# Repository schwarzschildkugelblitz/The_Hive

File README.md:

# The Hive 
The Following is Team Placeholders Solution to Flipkart's Grid 3.0

## About Grid 3.0

GRiD is Flipkart’s Flagship Engineering Campus Challenge which provides you the opportunity to apply your technical knowledge and skills, to compete and complete key challenges.

In its third edition, Flipkart GRiD becomes bigger & better, bringing Live Problem Statements from the world of E-Commerce to the brightest minds of India and lets you put your capabilities to the ultimate test.
## Problem  Statement

### Relay race - 4 Robots

1. Each robot has a package on top
2. Start positions are S1, S2, S3 & S4
3. Bot from S1 is expected to go to D1, Bot from S2 is expected to go to D2 and so on...
4. On start - Bot in the S1 location is expected to go to D1
5. On reaching D1 it should drop the item beyond the wall
6. Once the bot comes back to S1 (Completely inside S1 square), only then Bot from S2 can start
7. Race is over when S4 robot comes back to its square after dropping the parcel
No touching of the robots hardware/software is allowed once the race starts - Completely autonomous robots
Overall Arena size is 5 x 10ft

● Each block is 6x6in

● The grid is 1 cm tape / marking

● The brown line next to D1, D2, D3 & D4 is a 1-inch height wall

### Judging Criteria for Round I

Top 100 teams to finish the relay race (shortest time) - make it to Round II

### Deliverables for Round I
1. Pictures of Robots
2. Time taken to complete the relay race
3. Uninterrupted Video of the Relay Race - with Timer overlayed to indicate start and end of race - This
can be shot with a handheld or phone camera
4. Uninterrupted Video of Live Image Processing - with Timer overlayed to show how robots are being
tracked in real-time

## About The Team 

The Team consisted of the following members 
1. Harshit Batra 
2. Tanmay Vadhera
3. Mudit Aggarwal
4. Rohan Deswal
5. Drishti Adlakha 
6. Arjun Narula 
7. Harshit Kapoor
8. Mukul Gupta 
9. Vikas Poddar 
10. Soham

## Achitectrue

### Queen Tracking System 
### Transmission System
### Worker bee 

## Mechanical

## Electronics 
### Power system 
the worker bee is power by powerfull 7.2 V 2500 mah li-ion Battery

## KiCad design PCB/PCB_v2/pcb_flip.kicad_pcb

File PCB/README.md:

# PCB for Bot 

## Iteration 1 

Designed By Team Placeholders and Manufactured By PCB Powers 

### Dimensions

### Parts 

1. Arduino nano 
2. L293D
3. Power circuit 
4. NRF24 

### Funionality 

1. Driving bot's N20 Motor 
2. Driving bot's Servo Motor  
3. Receiving Data from Central Tracking system 

### Schmatic Diagram 

### 3D view 

## Iteration 2

Designed By Team Placeholders and Manufactured at CEDT lab,NSUT

### What's new 

1. Added boost cicuit 
2. Changed dimensions 

### Parts 

1. Arduino nano 
2. L293D
3. Power circuit 
4. NRF24 

### Funionality 
1. Driving bot's N20 Motor 
2. Driving bot's Servo Motor  
3. Receiving Data from Central Tracking system 

### Schmatic Diagram 

### 3D view

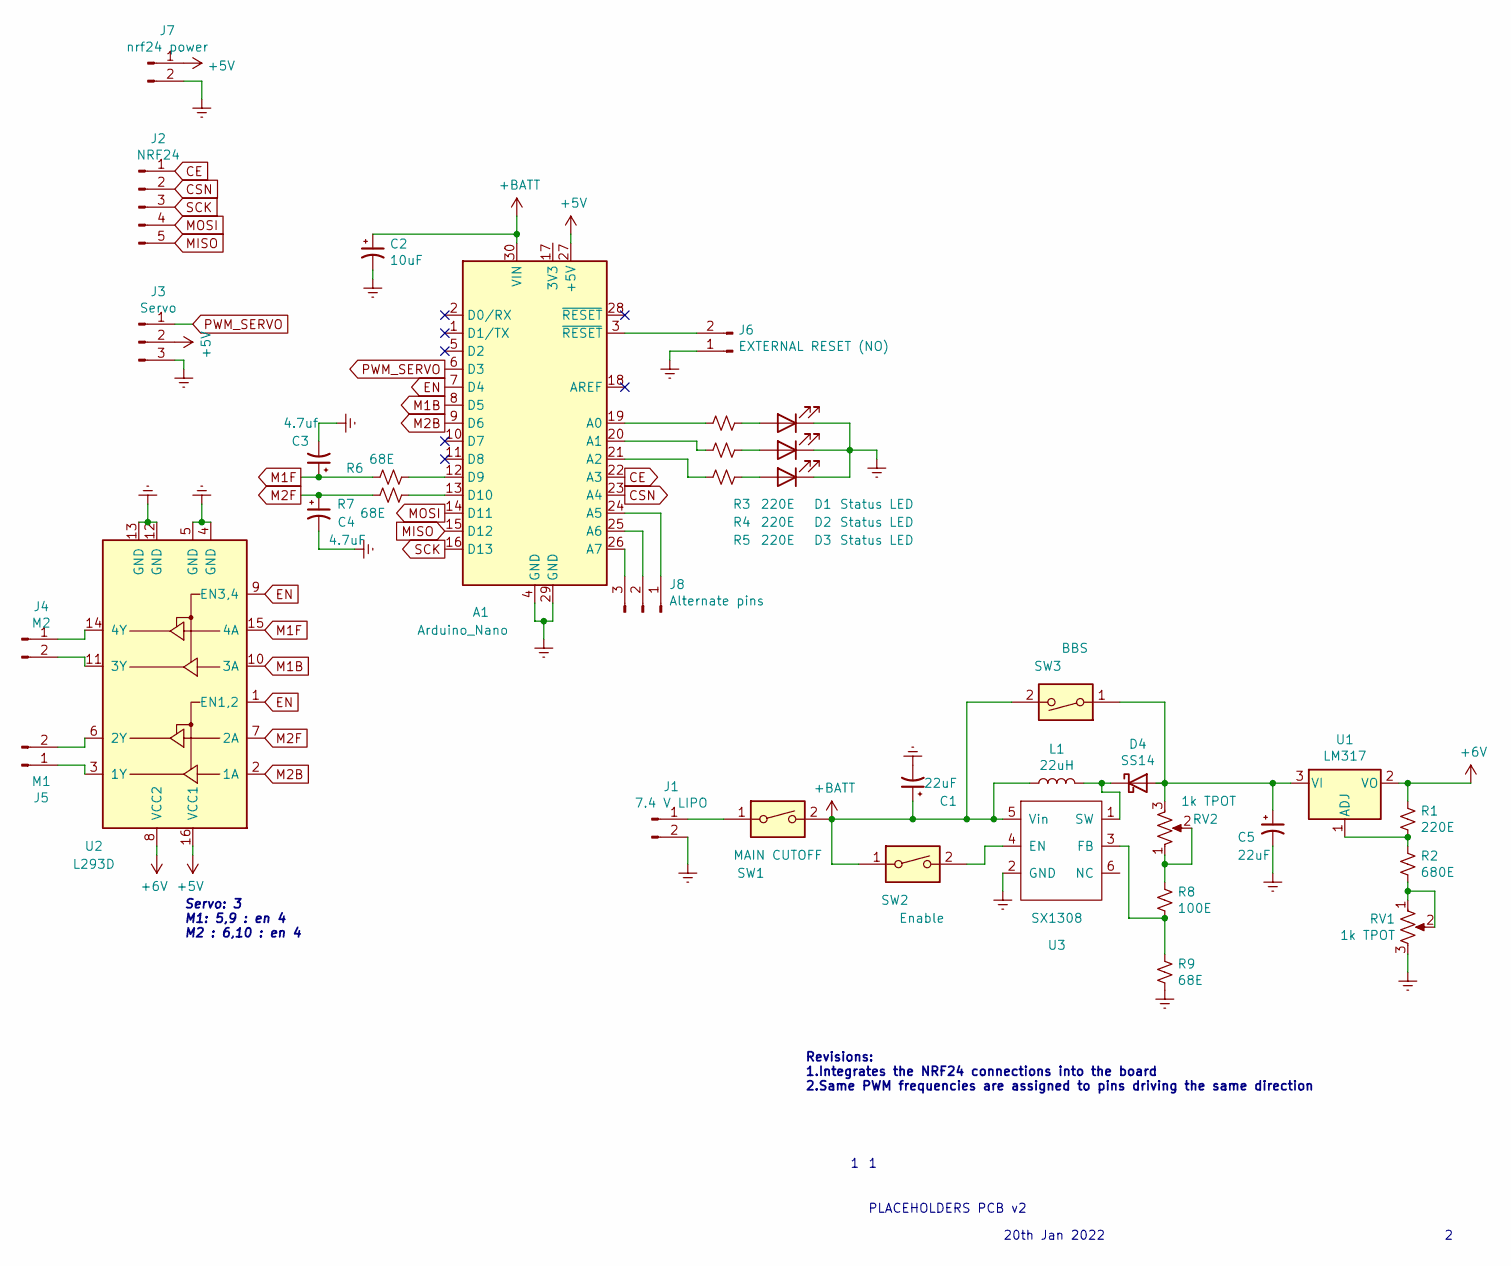
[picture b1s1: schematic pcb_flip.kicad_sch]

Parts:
A1: Arduino_Nano
C1, C5: 22uF; C_1206_3216Metric_Pad1.33x1.80mm_HandSolder
C2: 10uF; CP_EIA-3528-12_Kemet-T_Pad1.50x2.35mm_HandSolder
C3: 4.7uf; CP_EIA-3528-12_Kemet-T_Pad1.50x2.35mm_HandSolder
C4: 4.7uF; CP_EIA-3528-12_Kemet-T_Pad1.50x2.35mm_HandSolder
D1, D2, D3: Status LED; LED_D5.0mm_IRGrey
D4: SS14; D_1210_3225Metric_Pad1.42x2.65mm_HandSolder
J1: 7.4 V LIPO; JST_XH_B2B-XH-A_1x02_P2.50mm_Vertical
J2: NRF24; PinHeader_1x05_P2.54mm_Vertical
J3: Servo; PinHeader_1x03_P2.54mm_Vertical
J4: M2; TerminalBlock_Phoenix_MKDS-1,5-2_1x02_P5.00mm_Horizontal
J5: M1; TerminalBlock_Phoenix_MKDS-1,5-2_1x02_P5.00mm_Horizontal
J6: EXTERNAL RESET (NO); PinHeader_1x02_P2.54mm_Vertical
J7: nrf24 power; PinHeader_1x02_P2.54mm_Vertical
J8: Alternate pins; PinHeader_1x03_P2.54mm_Vertical
L1: 22uH; L_Radial_D6.0mm_P4.00mm
R1, R3, R4, R5: 220E; R_0805_2012Metric_Pad1.20x1.40mm_HandSolder
R2: 680E; R_0805_2012Metric_Pad1.20x1.40mm_HandSolder
R6, R7: 68E; R_0805_2012Metric_Pad1.20x1.40mm_HandSolder
R8: 100E; R_0805_2012Metric_Pad1.20x1.40mm_HandSolder
R9: 68E; C_0805_2012Metric_Pad1.18x1.45mm_HandSolder
RV1, RV2: 1k TPOT; Potentiometer_Bourns_3296W_Vertical
SW1: MAIN CUTOFF; JST_XH_B2B-XH-A_1x02_P2.50mm_Vertical
SW2: Enable; SolderJumper-2_P1.3mm_Open_TrianglePad1.0x1.5mm
SW3: BBS; SolderJumper-2_P1.3mm_Open_TrianglePad1.0x1.5mm
U1: LM317; TO-220-3_Vertical
U2: L293D; DIP-16_W7.62mm_Socket
U3: SX1308; SOT-23-6_Handsoldering

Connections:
+5V: A1.27 (+5V), J3.2, J7.1, U2.16 (VCC1); also elsewhere on the board
+6V: R1.1, U1.2 (VO), U2.8 (VCC2)
+BATT: A1.30 (VIN), C1.1, C2.1, L1.1, SW1.2, SW2.1, SW3.2, U3.5 (Vin)
CE: A1.22 (A3), J2.1; also elsewhere on the board
CSN: A1.23 (A4), J2.2; also elsewhere on the board
EN: A1.7 (D4), U2.1 (EN1,2), U2.9 (EN3,4)
Earth: A1.4 (GND), A1.29 (GND), C1.2, C2.2, C3.2, C4.2, C5.2, D1.1 (K), D2.1 (K), D3.1 (K), J1.2, J3.3, J6.1, J7.2, R9.2, RV1.3, U2.4 (GND), U2.5 (GND), U2.12 (GND), U2.13 (GND), U3.2 (GND); also elsewhere on the board
M1B: A1.8 (D5), U2.10 (3A)
M1F: C3.1, R6.2, U2.15 (4A)
M2B: A1.9 (D6), U2.2 (1A)
M2F: C4.1, R7.2, U2.7 (2A)
MISO: A1.15 (D12), J2.5; also elsewhere on the board
MOSI: A1.14 (D11), J2.4; also elsewhere on the board
unnamed: A1.3 (~RESET), J6.2
unnamed: A1.12 (D9), R6.1
unnamed: A1.13 (D10), R7.1
unnamed: A1.19 (A0), R3.2
unnamed: A1.20 (A1), R4.2
unnamed: A1.21 (A2), R5.2
unnamed: A1.24 (A5), J8.1
unnamed: A1.25 (A6), J8.2
unnamed: A1.26 (A7), J8.3
unnamed 22: C5.1, D4.2 (A), RV2.3, SW3.1, U1.3 (VI); also elsewhere on the board
unnamed: D1.2 (A), R3.1
unnamed: D2.2 (A), R4.1
unnamed: D3.2 (A), R5.1
unnamed 26: D4.1 (K), L1.2, U3.1 (SW); also elsewhere on the board
unnamed: J1.1, SW1.1
unnamed: J4.1, U2.14 (4Y)
unnamed: J4.2, U2.11 (3Y)
unnamed: J5.1, U2.3 (1Y)
unnamed: J5.2, U2.6 (2Y)
unnamed: R1.2, R2.1, U1.1 (ADJ)
unnamed: R2.2, RV1.1, RV1.2
unnamed: R8.1, RV2.1, RV2.2
unnamed: R8.2, R9.1, U3.3 (FB)
unnamed: SW2.2, U3.4 (EN)
PWM_SERVO: A1.6 (D3), J3.1
SCK: A1.16 (D13), J2.3; also elsewhere on the board

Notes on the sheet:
20th Jan 2022
PLACEHOLDERS PCB v2
Servo: 3 M1: 5,9 : en 4 M2 : 6,10 : en 4
Revisions: 1.Integrates the NRF24 connections into the board 2.Same PWM frequencies are assigned to pins driving the same direction

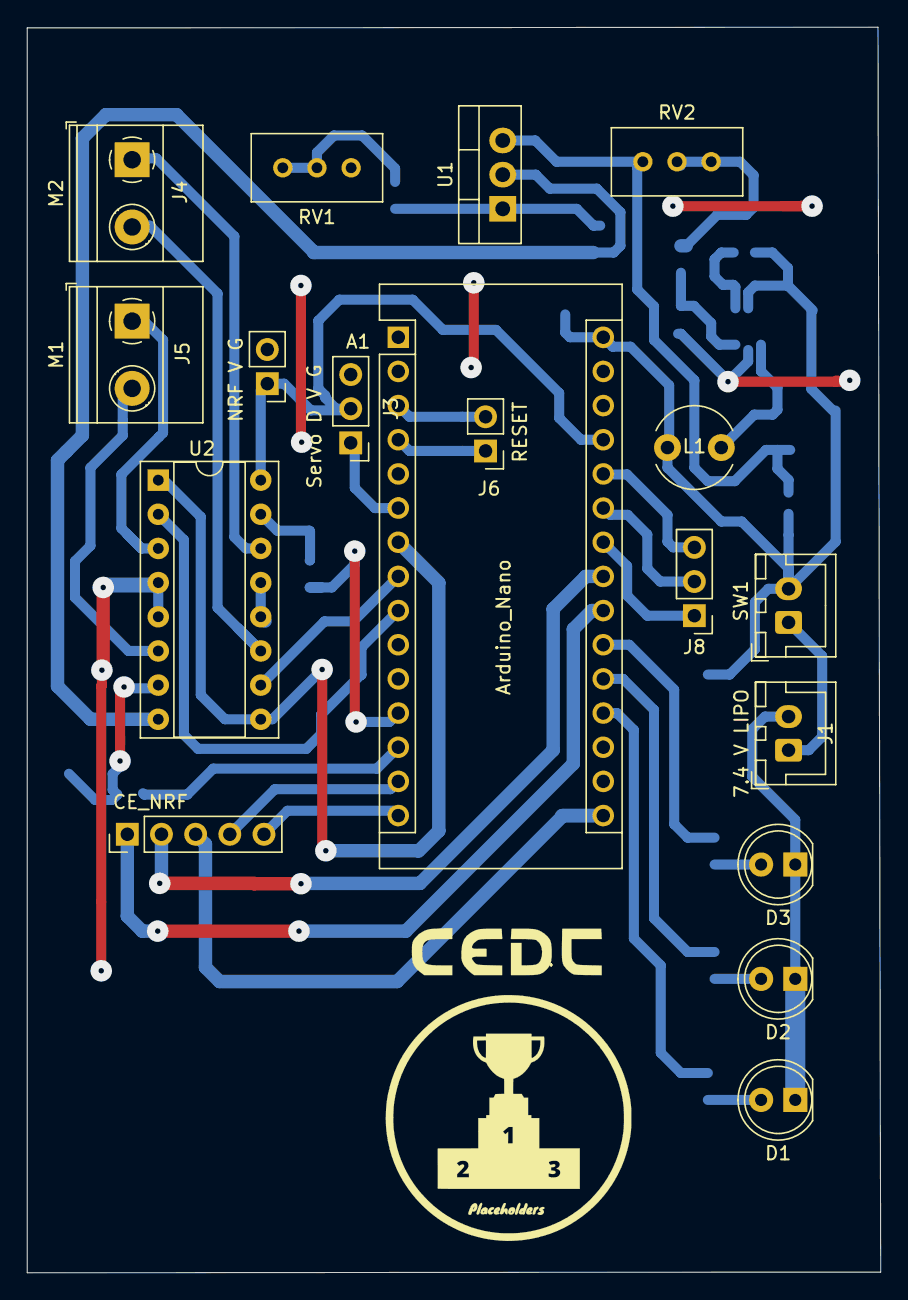
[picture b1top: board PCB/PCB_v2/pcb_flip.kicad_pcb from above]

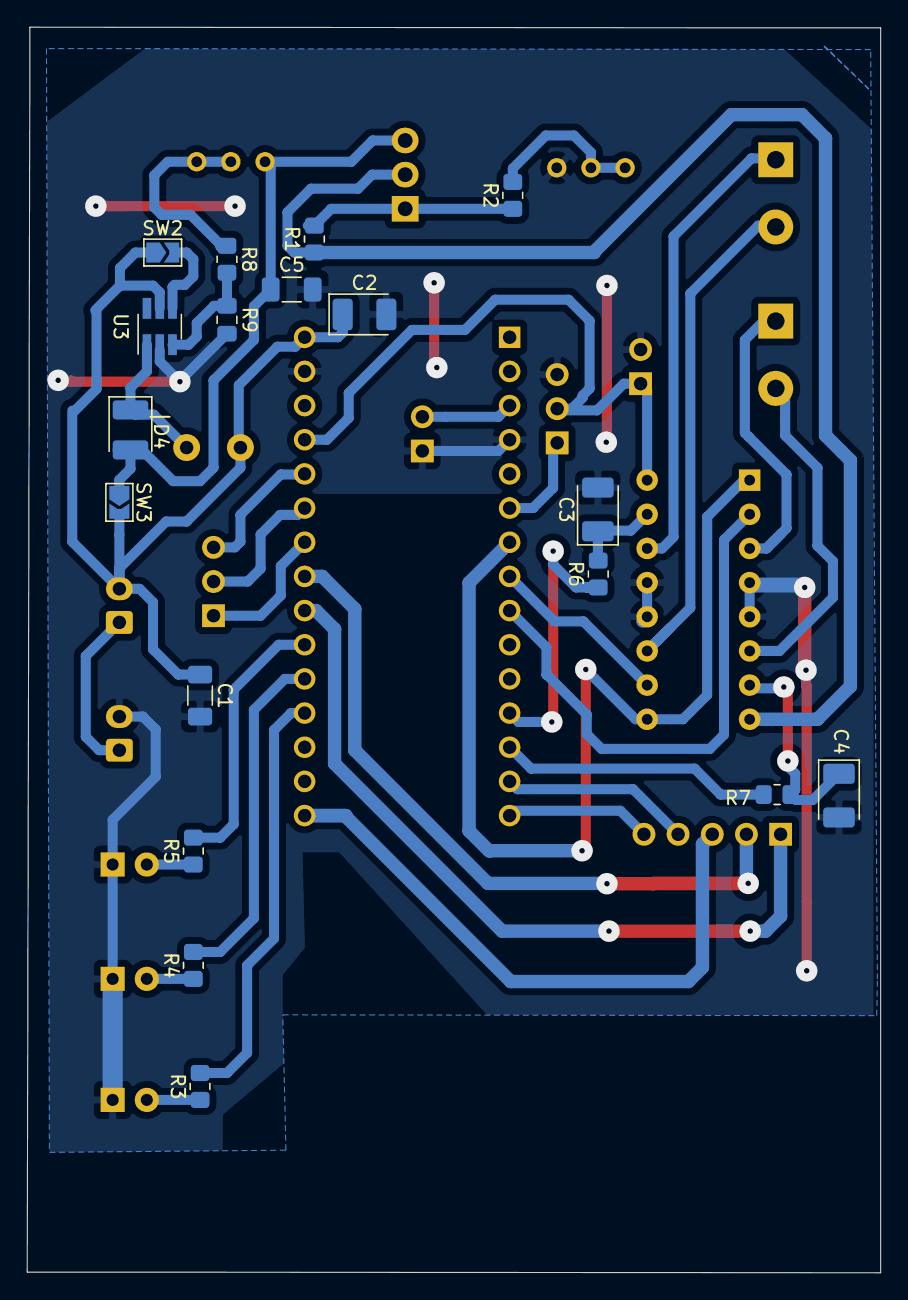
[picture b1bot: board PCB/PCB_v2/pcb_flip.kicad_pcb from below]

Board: 2 copper layers, 63.4 x 92.6 mm, 38 parts (18 on the bottom side), 39 nets.

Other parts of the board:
CE_NRF: NRF24; PinHeader_1x05_P2.54mm_Vertical
NRF V G: nrf24 power; PinHeader_1x02_P2.54mm_Vertical
RV2-24/01/2022: LOGO; placeholders
T V: LOGO; epp
|D4: SS14; D_1210_3225Metric_Pad1.42x2.65mm_HandSolder

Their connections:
+5V: NRF V G.1; also elsewhere on the board
CE: CE_NRF.1; also elsewhere on the board
CSN: CE_NRF.2; also elsewhere on the board
Earth: NRF V G.2; also elsewhere on the board
MISO: CE_NRF.5; also elsewhere on the board
MOSI: CE_NRF.4; also elsewhere on the board
unnamed 22: |D4.2; also elsewhere on the board
unnamed 26: |D4.1; also elsewhere on the board
SCK: CE_NRF.3; also elsewhere on the board

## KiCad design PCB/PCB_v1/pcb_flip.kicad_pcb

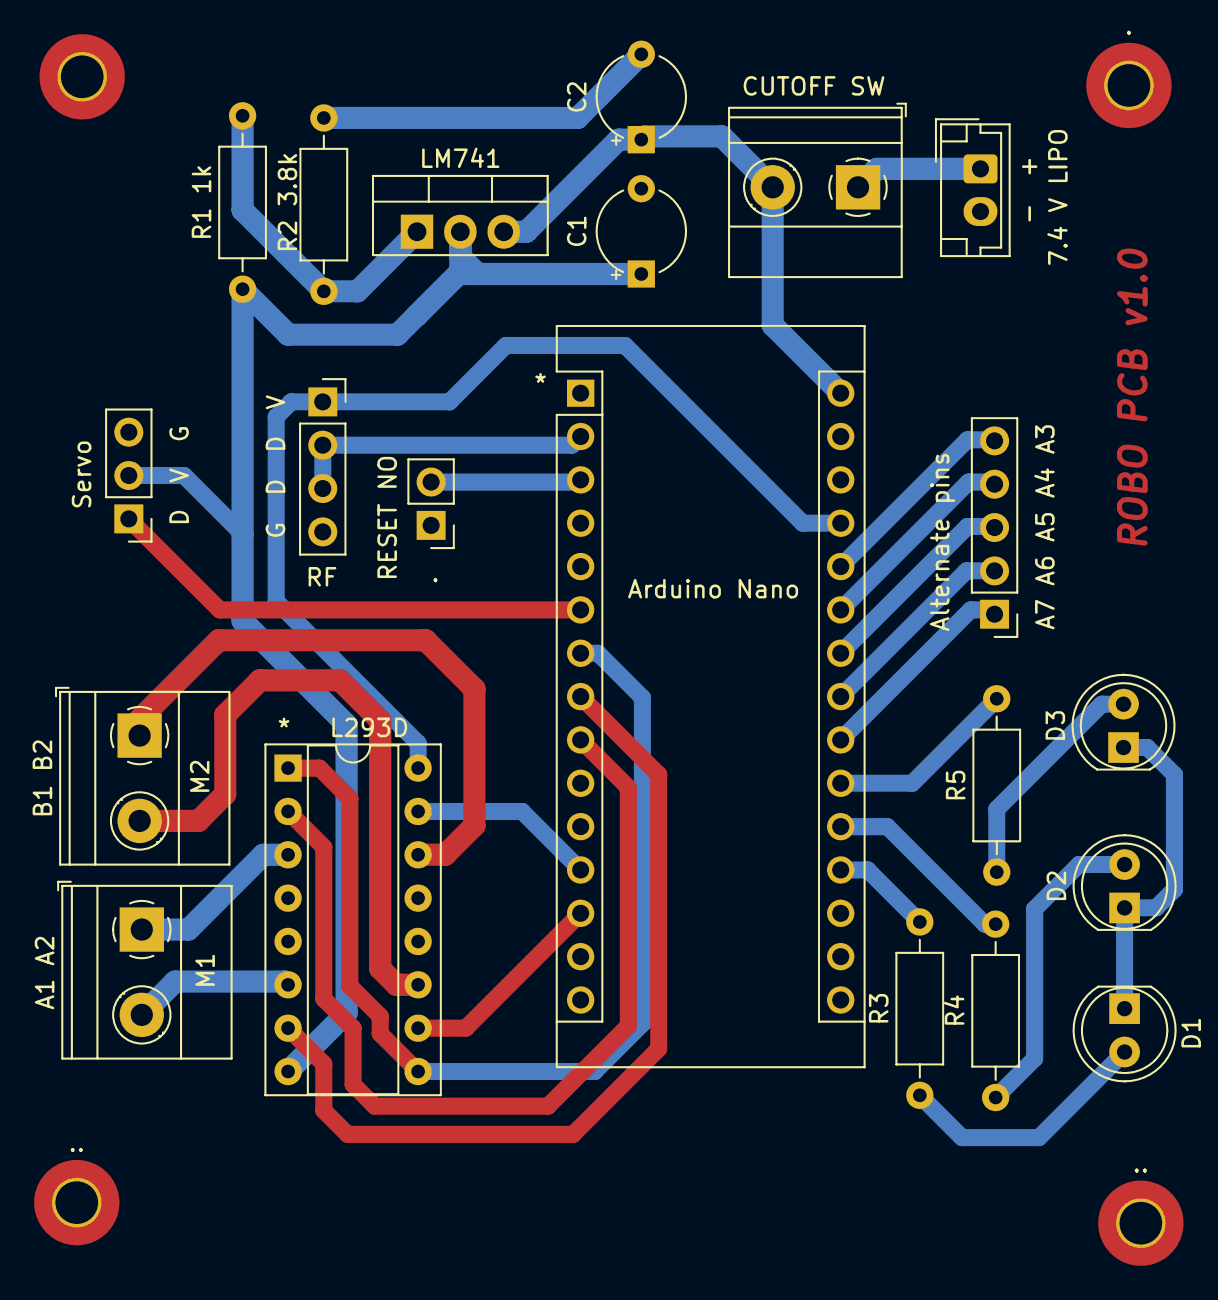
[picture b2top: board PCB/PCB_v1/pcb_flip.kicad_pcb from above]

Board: 2 copper layers, 25 parts (0 on the bottom side), 29 nets.

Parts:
 : .; MountingHole_2.5mm_Pad_TopBottom
*   L293D: L293D; DIP-16_W7.62mm_Socket
-  +: 7.4 V LIPO; JST_EH_B2B-EH-A_1x02_P2.50mm_Vertical
., .., ..#2: .; MountingHole_2.5mm_Pad_TopBottom
.#2: RESET NO; PinHeader_1x02_P2.54mm_Vertical
A7 A6 A5 A4 A3: Alternate pins; PinHeader_1x05_P2.54mm_Vertical
Arduino Nano: *; Arduino_Nano
C1, C2: 1uf; CP_Radial_Tantal_D5.0mm_P5.00mm
CUTOFF SW: MAIN CUTOFF; TerminalBlock_Phoenix_MKDS-1,5-2_1x02_P5.00mm_Horizontal
D1, D2, D3: Status LED; LED_D5.0mm
D  V  G: Servo; PinHeader_1x03_P2.54mm_Vertical
LM741: LM317; TO-220-3_Vertical
M1: A1 A2; TerminalBlock_Phoenix_MKDS-1,5-2_1x02_P5.00mm_Horizontal
M2: B1 B2; TerminalBlock_Phoenix_MKDS-1,5-2_1x02_P5.00mm_Horizontal
R1 1k: 1k; R_Axial_DIN0207_L6.3mm_D2.5mm_P10.16mm_Horizontal
R2 3.8k: 3.8k; R_Axial_DIN0207_L6.3mm_D2.5mm_P10.16mm_Horizontal
R3, R4, R5: 220E; R_Axial_DIN0207_L6.3mm_D2.5mm_P10.16mm_Horizontal
RF: G D D V; PinSocket_1x04_P2.54mm_Vertical

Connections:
+5V: * L293D.16, Arduino Nano.27, RF.1
+6V: * L293D.8, C1.1, D V G.2, LM741.2, R1 1k.1
+BATT: Arduino Nano.30, C2.1, CUTOFF SW.2, LM741.3
Earth: * L293D.4, * L293D.5, * L293D.12, * L293D.13, - +.2, .#2.1, Arduino Nano.4, Arduino Nano.29, C1.2, C2.2, D1.1, D2.1, D3.1, D V G.3, R2 3.8k.2, RF.4
unnamed: Arduino Nano.2, RF.2, RF.3
unnamed: .#2.2, Arduino Nano.3
unnamed: Arduino Nano.6, D V G.1
unnamed: * L293D.1, * L293D.9, Arduino Nano.7
unnamed: * L293D.7, Arduino Nano.8
unnamed: * L293D.2, Arduino Nano.9
unnamed: * L293D.15, Arduino Nano.12
unnamed: * L293D.10, Arduino Nano.13
unnamed: Arduino Nano.19, R3.2
unnamed: Arduino Nano.20, R4.2
unnamed: Arduino Nano.21, R5.2
unnamed: A7 A6 A5 A4 A3.1, Arduino Nano.22
unnamed: A7 A6 A5 A4 A3.2, Arduino Nano.23
unnamed: A7 A6 A5 A4 A3.3, Arduino Nano.24
unnamed: A7 A6 A5 A4 A3.4, Arduino Nano.25
unnamed: A7 A6 A5 A4 A3.5, Arduino Nano.26
unnamed: D1.2, R3.1
unnamed: D2.2, R4.1
unnamed: D3.2, R5.1
unnamed: - +.1, CUTOFF SW.1
unnamed: * L293D.14, M2.1
unnamed: * L293D.11, M2.2
unnamed: * L293D.3, M1.1
unnamed: * L293D.6, M1.2
unnamed: LM741.1, R1 1k.2, R2 3.8k.1

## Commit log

2021-06-25 created folder for machine learning model
2021-06-26 Create pcb_design
2021-06-26 Add files via upload
    Main circuit board for the robot.
2021-06-28 Implemented tracking markers and added perspective correction
2021-06-29 fixed some array parsing errors
2021-07-28 Updated problem statement and other pdfs
2021-08-31 Increased number of markers
2021-09-04 added text to video
2021-09-04 Rename main_body/ROBOT_W_changes v3.step to mechanical/ ROBOT_W_changes v3.step
2021-09-04 Create h
2021-09-04 added official information Given by the Organizer
2021-09-04 added readme
2021-09-04 Rename mechanical/ROBOT_W_changes v3.step to CAD_Model/ROBOT_W_changes v3.step
2021-09-05 Serial and Control classes added, code made more generalized
2021-09-05 Doc strings added
2021-09-07 added communication detalis
    0-3 bits address
    case 1 - angle(in degrees) 2 decimal precision
    - distance (in cm ) 2 decimal places
    case 2 - 0 stop 1 right 2 left 3 drop 4 slow drive
2021-09-10 Rename servo_calibration.ino to worker_bee/servo_calibration.ino
2021-09-19 PID system added, initial system altered, code is undocumented
2021-09-20 Rename serial_comm/serial_comm/reception/reception.ino to worker_bee/reception/reception.ino
2021-09-20 Rename serial_comm/serial_comm/transmission/transmission.ino to workerbee/transmission/transmission.ino
2021-09-20 Rename workerbee/transmission/transmission.ino to worker_beetransmissiontransmission.ino
2021-09-20 Rename worker_beetransmissiontransmission.ino to worker_bee/transmission/transmission.ino
2021-09-20 Create miscellaneous
2021-09-20 Rename miscellaneous to Miscellaneous/hhh
2021-09-28 Using only single camera, PID system updated, code refactored
2021-09-29 Final working code for round 1 tuned PID, changes in path calculation
2021-09-29 changed special commands
2021-10-01 minor changes made code better
2021-10-01 fixed minor bug
2021-10-03 Some changes to docstrings and refactoring
2021-11-09 Testing Edit
2021-12-01 frontend layout updated
2021-12-24 1st Round final working code
2021-12-24 changed design of dashboard
    changes made in frontend
2021-12-25 all files added
2021-12-25 Frontend updated
    front end layout changed and improved
2021-12-25 Frontend updated
    frontend layout changed and improved
2021-12-26 added live video
2021-12-29 changes in backend
2021-12-29 minor changes
2021-12-29 Round 2 1st attempt code
2022-01-01 Add files via upload
    stop button integration
2022-01-02 round 2 code,m PID adjusted
2022-01-04 Added Astar Visualisation Tool
2022-01-04 Adjusted PID Values with True Divide Error Fix
2022-01-04 Updated Value Adjustments for difference in motor speeds
2022-01-04 Added Code for KIll Switch
2022-01-04 PEP8 Compliance Check
2022-01-04 Revert "Add files via upload"
2022-01-04 Stop Button Integration in round_2 branch
2022-01-05 round 2 collision detection and multiprocessing
2022-01-06 without pathfinding implemented
2022-01-06 without pathfinding implemented and few runs tested
2022-01-07 Path Finding Completed
2022-01-07 pathfinding ind-1 completed and ind-2 to be checked 😊
2022-01-07 minor changes in frontend fixed minor bugs
2022-01-08 Updated astar.py added check to minimize turning by changing heuritic measurement
    minimized turns in path finding
2022-01-08 updated astar.py
2022-01-08 Path Finding And Drop Alignment
2022-01-08 Reverted Back to Pre Drop AligningRevert "updated astar.py"
    This reverts commit cbd10ec3fde4a2e8de5573e28950942e1b3babec.
2022-01-08 serial pipe implemented
2022-01-08 PathFinder Drop Alignment Implemented
2022-01-10 Refactored Path Finder and Astar and seperated into two files
2022-01-10 Path Finder and Astar Refactored
2022-01-10 Initial Path Alignment Update
2022-01-10 priority target hit check implemented
2022-01-10 turning to be tuned
2022-01-12 round 2 working for 1 bot
2022-01-12 Space Offset Updated
2022-01-13 Additional Drop Chute Offset Added
2022-01-14 hot milfs in my area
2022-01-17 added error in astar
2022-01-17 testing improved astar
2022-01-18 1 bot properly working
2022-01-18 Alternate Path Gen Implemented
2022-01-18 Alternate Path Gen Bug Fixxes
2022-01-18 almost ready for testing round 2 multiple
2022-01-18 almost ready for testing round 2 multiple (fixed)
2022-01-18 A* Nuked
2022-01-19 control system minor changes
2022-01-19 Round 2 smart threshold to be implemented
2022-01-19 1 test done
2022-01-20 command delay properly added
2022-01-25 Post Round 2 Submission
2022-01-27 PEP8 Compliance Update
2022-01-27 added readme for PCB
2022-01-27 Added boost circuitry and optimized pin mappings
2022-01-27 grid added to frontend
2022-01-28 documentation added
2022-01-28 removed unused library
2022-01-31 made code organized and readable , removed redundancy
2022-03-20 Documentation updated
